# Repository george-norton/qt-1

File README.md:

# QT-1

QT-1 is a ZMK based Lego remote, it also works as a keyboard - so it could be used as a remote for a TV too.

## Features

- ZMK studio support for remapping buttons
- Connect to up to 8 hubs at the same time
- Control up to 64 motors
- Motor speed control on a layer

## Links

- [Firmware source code](https://github.com/george-norton/zmk-keyboard-qt-1)
- [Bluetooth hub control ZMK module](https://github.com/george-norton/zmk-behavior-ble-lego-control)
- [ZMK Studio for remapping buttons](https://zmk.studio/)

## Hub compatability

QT-1 has been tested with the following hubs:
- WeDo 2.0 hub
- Lego PoweredUp! 4 port technic hub
- A 3rd party Power Functions hub (advertises as "JG_JMC-3D34")

I expect most other modern Lego hubs to work too.

## How to build

This is a DIY project, the idea is that you purchase PCBs from a manufacturer (JLCPCB, PCBWay etc..), 3D print the case and assemble it yourself. Details build instructions will follow at a later date.

You will need the following:
- Soldering iron
- Unleaded solder (this is a toy)
- Screwdriver to match the screws you choose
- Optional hot glue gun to make an LED diffuser

Bill of materials:

| Quantity     | Part                            | Description                                                                                                                             |
| ------------ | ------------------------------- | --------------------------------------------------------------------------------------------------------------------------------------- |
| 10           | [Alps SKPMAME010 switches](https://www.lcsc.com/product-detail/C115348.html)        | The main controller buttons. This variant has a low actuation force. Cheaper clones are available but may require more force to press.  |
| 1 (optional) | [B3U-1000P](https://www.lcsc.com/product-detail/C231329.html)                       | Optional reset button.                                                                                                                  |
| 1 (optional) | 0805 LED                        | Optional status LED.                                                                                                                    |
| 1 (optional) | 0603 Resistor (68-100ohm)       | Current limiting resistor for the status LED. The LED must not pull more than 15mA from the GPIO pin.                                   |
| 1            | Nice!Nano v2 or clone           | nrf52 based ProMicro form factor microcontroller board.                                                                                 |
| 2            | [4mm tall 1x12 pin header](https://www.aliexpress.com/item/4001122376295.html) | Needs to be 4mm to leave space for the battery, and for the USB socket to align.                                                        |
| 1            | 301230 battery with JST-PH plug | Lipo battery.                                                                                                                           |
| 1            | [S2B-PH-K](https://www.lcsc.com/product-detail/C19723656.html?)                        | 2 pin JST-PH socket.                                                                                                                    |
| 1 (optional) | [MSS22D18G2 125](https://www.lcsc.com/product-detail/C2906278.html)                  | Power switch                                                                                                                            |
| 1            | QT-1 PCB                        |                                                                                                                                         |
| 1            | 3D Printed case                 | FDM printed in PLA (mine were ordered from JLCPCB)                                                                                      |
| 2            | M3 5mm Heat-set insert          |                                                                                                                                         |
| 2            | M3 countersunk screw 10 or 12mm | These are visible from the front - consider coloured screws.                                                                            |

### Tips
- Take care soldering the switches - they are easy to melt if you nick them with your soldering iron.
- To solder switches, tin on pad, add some flux, place the switch then reheat the solder.
- If a switch is miss-aligned the top case will not fit. Solder the switches on one side then check everything fits before soldering on the other sides.

## Firmware

Grab prebuilt firmware from [here](https://github.com/george-norton/zmk-keyboard-qt-1/releases/), connect the remote to a computer via the USB port and double ta the reset button (or short the pads twice if no button is installed) to put it into bootloader mode. Then drag and drop the uf2 file to the drive that appears.

Once you are running QT-1 firmware, you can press the two centre buttons together to go into bootloader mode.

## Default Keymap

- The two d-pads control motors.
- The top middle button pairs hubs when pressed and turns the controller off when held.
- The bottom middle button toggles between the motor control layer and the speed control layer.
- Pressing the to middle buttons together puts the controller into bootloader mode.

## Schematic

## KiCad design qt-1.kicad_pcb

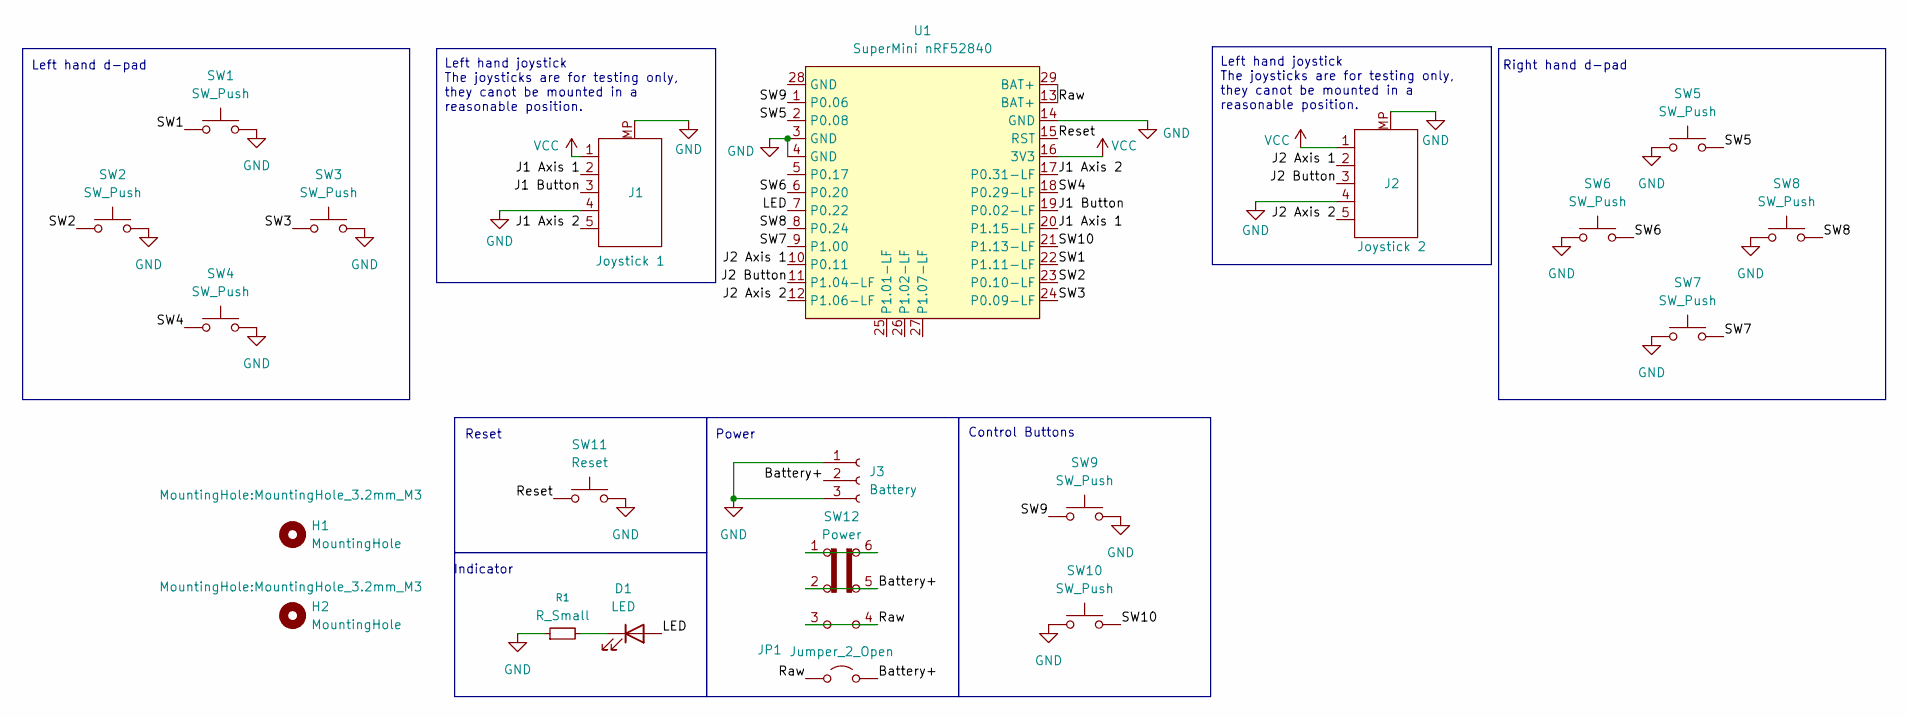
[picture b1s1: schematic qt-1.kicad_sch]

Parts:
D1: LED; LED_0805_2012Metric_Pad1.15x1.40mm_HandSolder
H1, H2: MountingHole; MountingHole_3.2mm_M3
J1: Joystick 1; FPC_5_TopContact
J2: Joystick 2; FPC_5_TopContact
J3: Battery; Swappable_JST_PH_S2B-PH-K_1x03_P2.00mm_Horizontal
JP1: Jumper_2_Open; SolderJumper-2_P1.3mm_Open_TrianglePad1.0x1.5mm
R1: R_Small; R_0603_1608Metric_Pad0.98x0.95mm_HandSolder
SW1, SW2, SW3, SW4, SW5, SW6, SW7, SW8, SW9, SW10: SW_Push; Alps SKPM TACT switch
SW11: Reset; SW_SPST_B3U-1000P
SW12: Power; DPDT_MSS22D18G2
U1: SuperMini nRF52840; SuperMini_nRF52840_AH_USBup

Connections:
/Battery+: J3.2, JP1.2 (B), SW12.2 (B), SW12.5 (B)
/J1 Axis 1: J1.2, U1.20 (P1.15-LF)
/J1 Axis 2: J1.5, U1.17 (P0.31-LF)
/J1 Button: J1.3, U1.19 (P0.02-LF)
/J2 Axis 1: J2.2, U1.10 (P0.11)
/J2 Axis 2: J2.5, U1.12 (P1.06-LF)
/J2 Button: J2.3, U1.11 (P1.04-LF)
/LED: D1.2 (A), U1.7 (P0.22)
/Raw: JP1.1 (A), SW12.3 (C), SW12.4 (A), U1.13 (BAT+), U1.29 (BAT+)
/Reset: SW11.1, U1.15 (RST)
/SW1: SW1.1, U1.22 (P1.11-LF)
/SW2: SW2.1, U1.23 (P0.10-LF)
/SW3: SW3.1, U1.24 (P0.09-LF)
/SW4: SW4.1, U1.18 (P0.29-LF)
/SW5: SW5.2, U1.2 (P0.08)
/SW6: SW6.2, U1.6 (P0.20)
/SW7: SW7.2, U1.9 (P1.00)
/SW8: SW8.2, U1.8 (P0.24)
/SW9: SW9.1, U1.1 (P0.06)
/SW10: SW10.2, U1.21 (P1.13-LF)
GND: J1.4, J1.MP, J2.4, J2.MP, J3.1, J3.3, R1.1, SW1.2, SW2.2, SW3.2, SW4.2, SW5.1, SW6.1, SW7.1, SW8.1, SW9.2, SW10.1, SW11.2, U1.3 (GND), U1.4 (GND), U1.14 (GND)
unnamed: D1.1 (K), R1.2
unnamed: SW12.1 (A), SW12.6 (C)
VCC: J1.1, J2.1, U1.16 (3V3)

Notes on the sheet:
Left hand joystick The joysticks are for testing only, they canot be mounted in a reasonable position.
Left hand d-pad
Right hand d-pad
Reset
Indicator
Power
Control Buttons

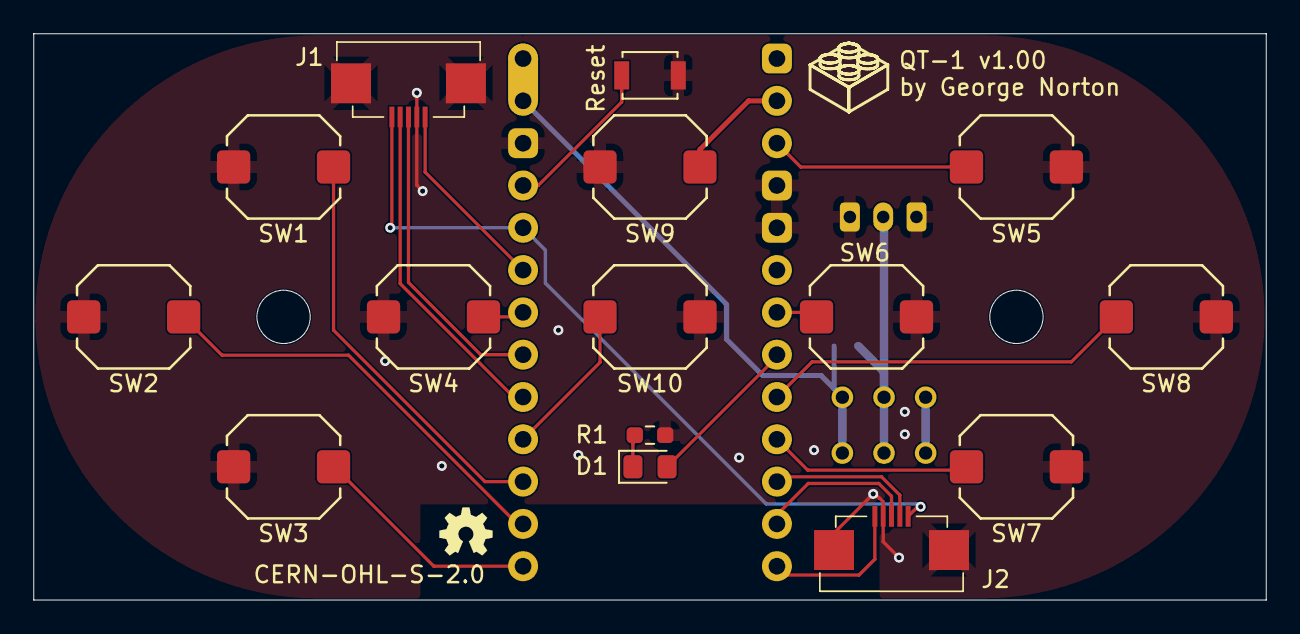
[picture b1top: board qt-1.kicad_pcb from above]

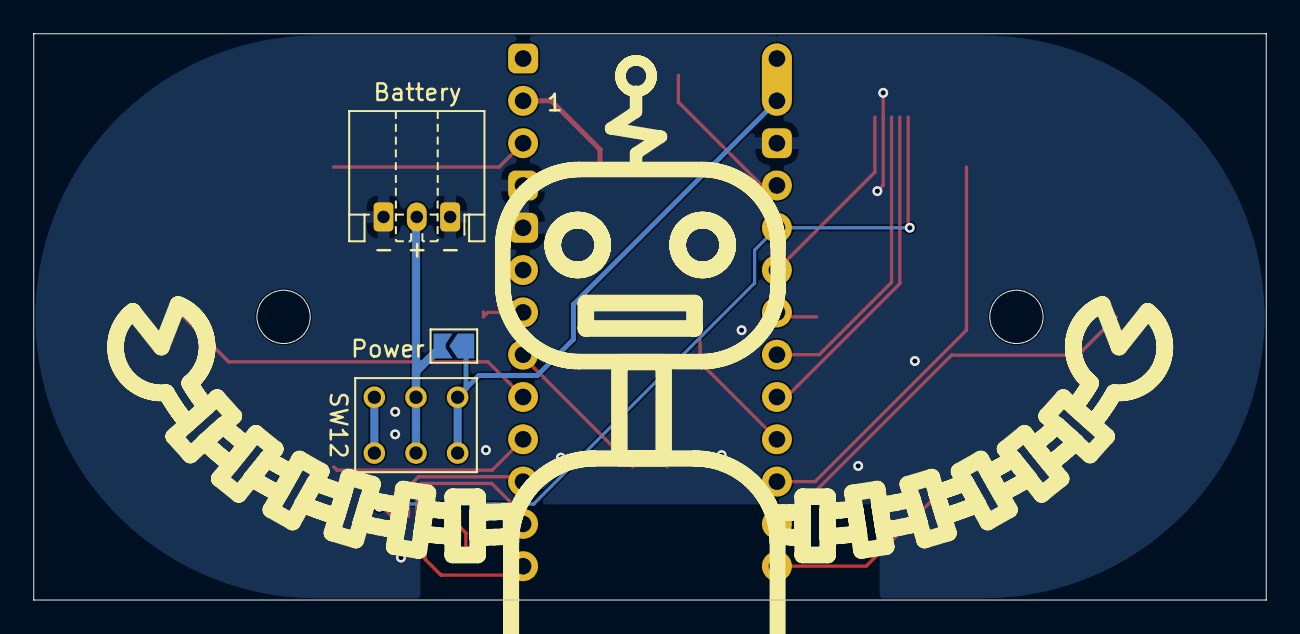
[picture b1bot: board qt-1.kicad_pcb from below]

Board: 2 copper layers, 74.0 x 34.0 mm, 21 parts (4 on the bottom side), 24 nets.

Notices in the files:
qt-1.kicad_pcb:
CERN-OHL-S-2.0
